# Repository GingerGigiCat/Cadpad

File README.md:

# Cadpad
This is my [hackpad](https://hackpad.hackclub.com/) for CAD!

Specifically, it's with onshape in my mind. The 5 buttons are, going clockwise from the top right, New sketch, Normal to sketch plane, Extrude, Deselect all, Fillet

Do excuse the tallness of my schematic

# BOM
- 1x SEEED XIAO RP2040
- 5x MX style switches and keycaps
- 4x M3 threaded inserts with screws

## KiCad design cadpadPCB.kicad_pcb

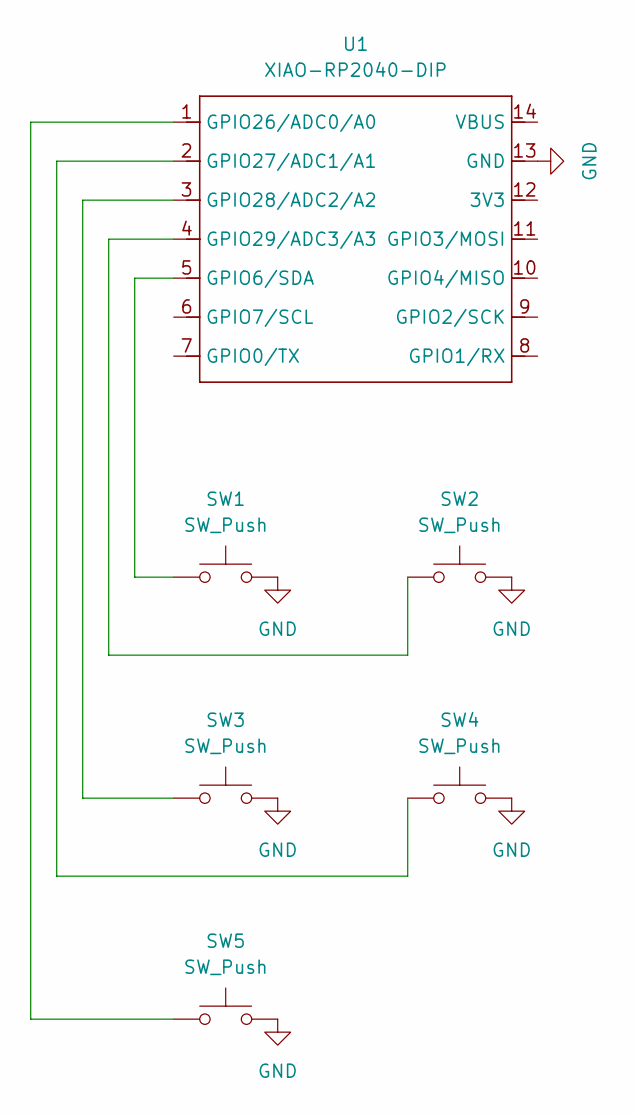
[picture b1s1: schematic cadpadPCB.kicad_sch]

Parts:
SW1, SW2, SW3, SW4, SW5: SW_Push; SW_Cherry_MX_1.00u_PCB
U1: XIAO-RP2040-DIP

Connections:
GND: SW1.2, SW2.2, SW3.2, SW4.2, SW5.2, U1.13 (GND)
unnamed: SW1.1, U1.5 (GPIO6/SDA)
unnamed: SW5.1, U1.1 (GPIO26/ADC0/A0)
unnamed: SW4.1, U1.2 (GPIO27/ADC1/A1)
unnamed: SW3.1, U1.3 (GPIO28/ADC2/A2)
unnamed: SW2.1, U1.4 (GPIO29/ADC3/A3)

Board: 2 copper layers, 6 parts (0 on the bottom side), 6 nets, no tracks yet.

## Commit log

2025-08-01 code!
2025-08-01 readme!!
2025-08-01 add files!!!!
